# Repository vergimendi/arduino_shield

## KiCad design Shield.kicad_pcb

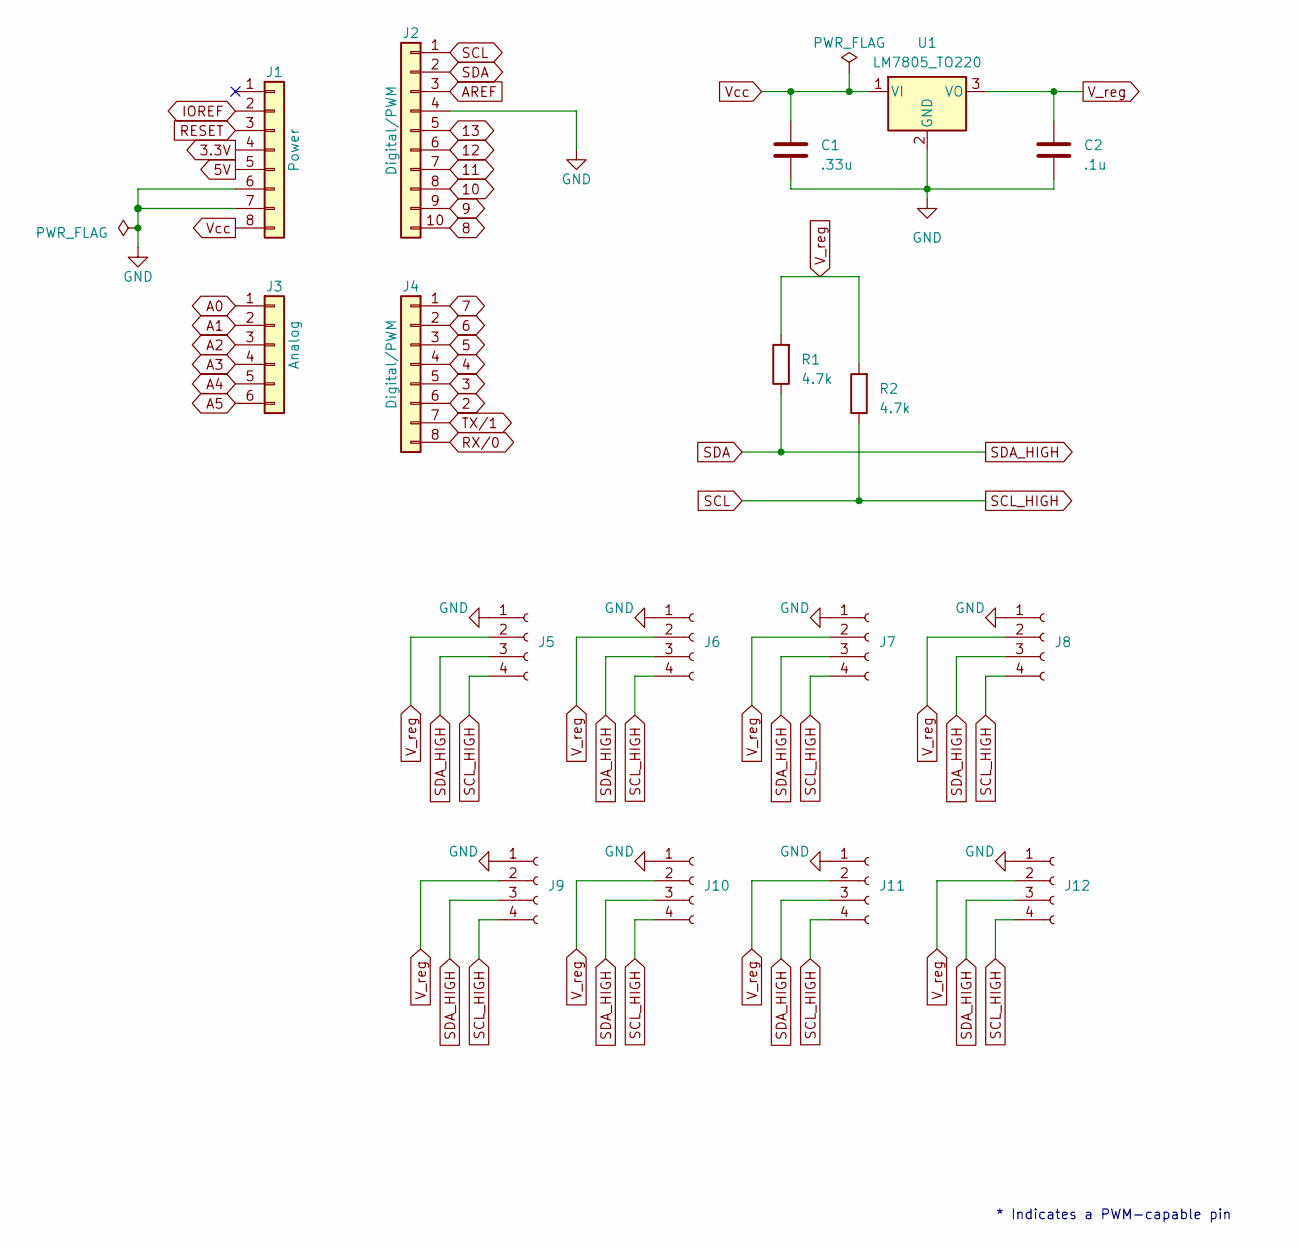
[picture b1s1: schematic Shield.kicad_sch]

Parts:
C1: .33u; C_0805_2012Metric_Pad1.18x1.45mm_HandSolder
C2: .1u; C_0805_2012Metric_Pad1.18x1.45mm_HandSolder
J1: Power; PinSocket_1x08_P2.54mm_Vertical
J2: Digital/PWM; PinSocket_1x10_P2.54mm_Vertical
J3: Analog; PinSocket_1x06_P2.54mm_Vertical
J4: Digital/PWM; PinSocket_1x08_P2.54mm_Vertical
J5, J6, J7, J8, J9, J10, J11, J12: Conn_01x04_Socket; JST_XH_B4B-XH-A_1x04_P2.50mm_Vertical
R1, R2: 4.7k; R_0805_2012Metric_Pad1.20x1.40mm_HandSolder
U1: LM7805_TO220; TO-220-3_Vertical

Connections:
2: J4.6
3: J4.5
3.3V: J1.4
4: J4.4
5: J4.3
5V: J1.5
6: J4.2
7: J4.1
8: J2.10
9: J2.9
10: J2.8
11: J2.7
12: J2.6
13: J2.5
A0: J3.1
A1: J3.2
A2: J3.3
A3: J3.4
A4: J3.5
A5: J3.6
AREF: J2.3
GND: C1.1, C2.1, J1.6, J1.7, J2.4, J5.1, J6.1, J7.1, J8.1, J9.1, J10.1, J11.1, J12.1, U1.2 (GND)
IOREF: J1.2
RESET: J1.3
RX/0: J4.8
SCL: J2.1, J5.4, J6.4, J7.4, J8.4, J9.4, J10.4, J11.4, J12.4, R2.1
SDA: J2.2, J5.3, J6.3, J7.3, J8.3, J9.3, J10.3, J11.3, J12.3, R1.1
TX/1: J4.7
V_reg: C2.2, J5.2, J6.2, J7.2, J8.2, J9.2, J10.2, J11.2, J12.2, R1.2, R2.2, U1.3 (VO)
Vcc: C1.2, J1.8, U1.1 (VI)

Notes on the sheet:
* Indicates a PWM-capable pin

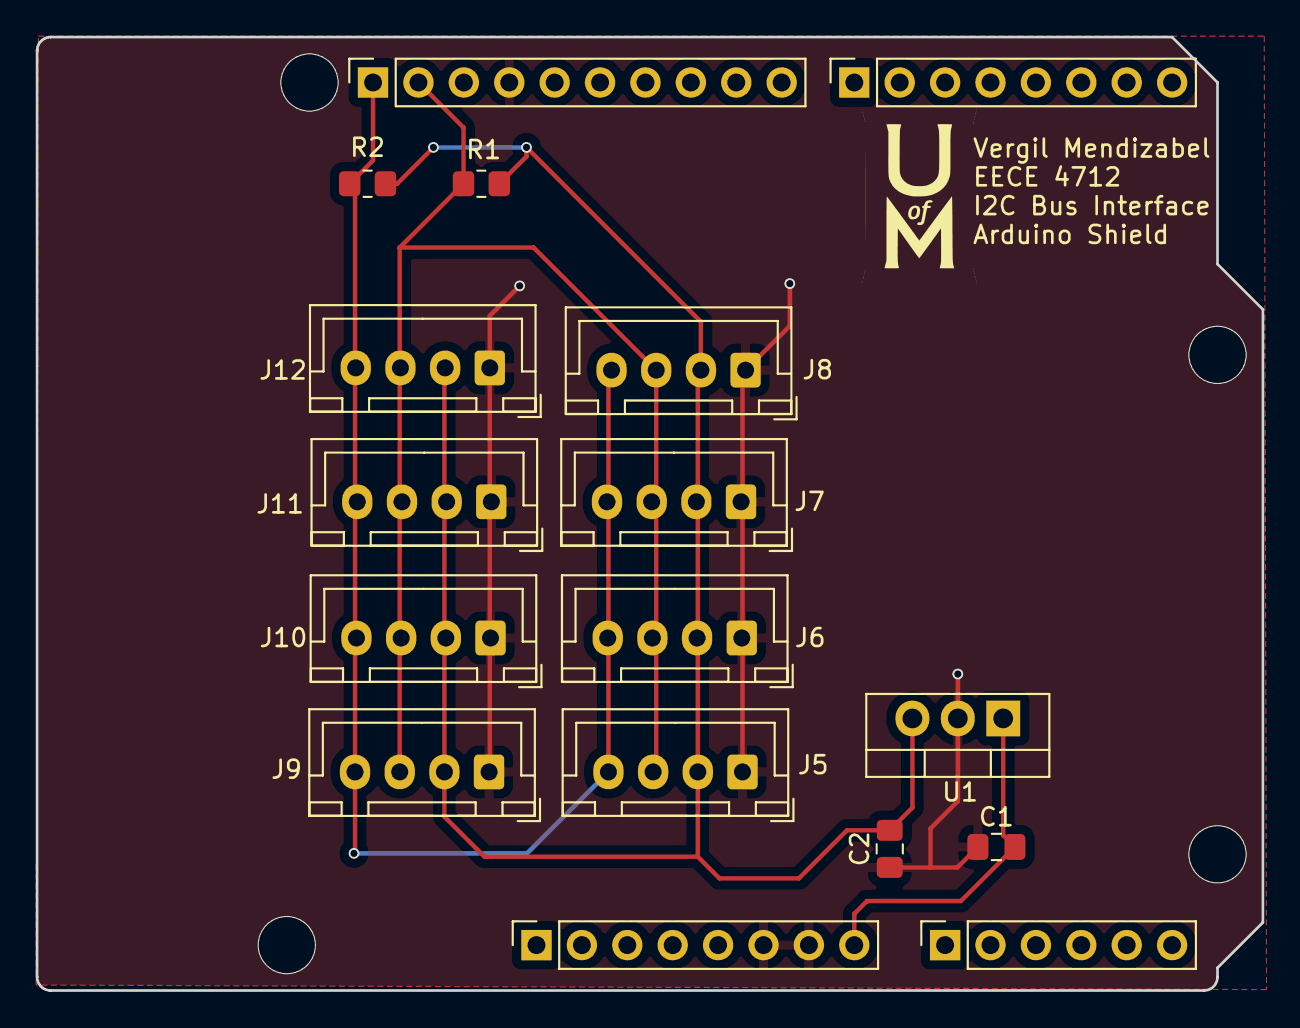
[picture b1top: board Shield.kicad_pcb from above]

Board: 2 copper layers, 68.6 x 53.3 mm, 21 parts (0 on the bottom side), 5 nets.

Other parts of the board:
MH1, MH2, MH3, MH4: MountingHole_3.2mm
